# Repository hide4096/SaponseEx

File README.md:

# SaponseEx
マイクロマウス
RT社HM-Starterキットをベースに開発

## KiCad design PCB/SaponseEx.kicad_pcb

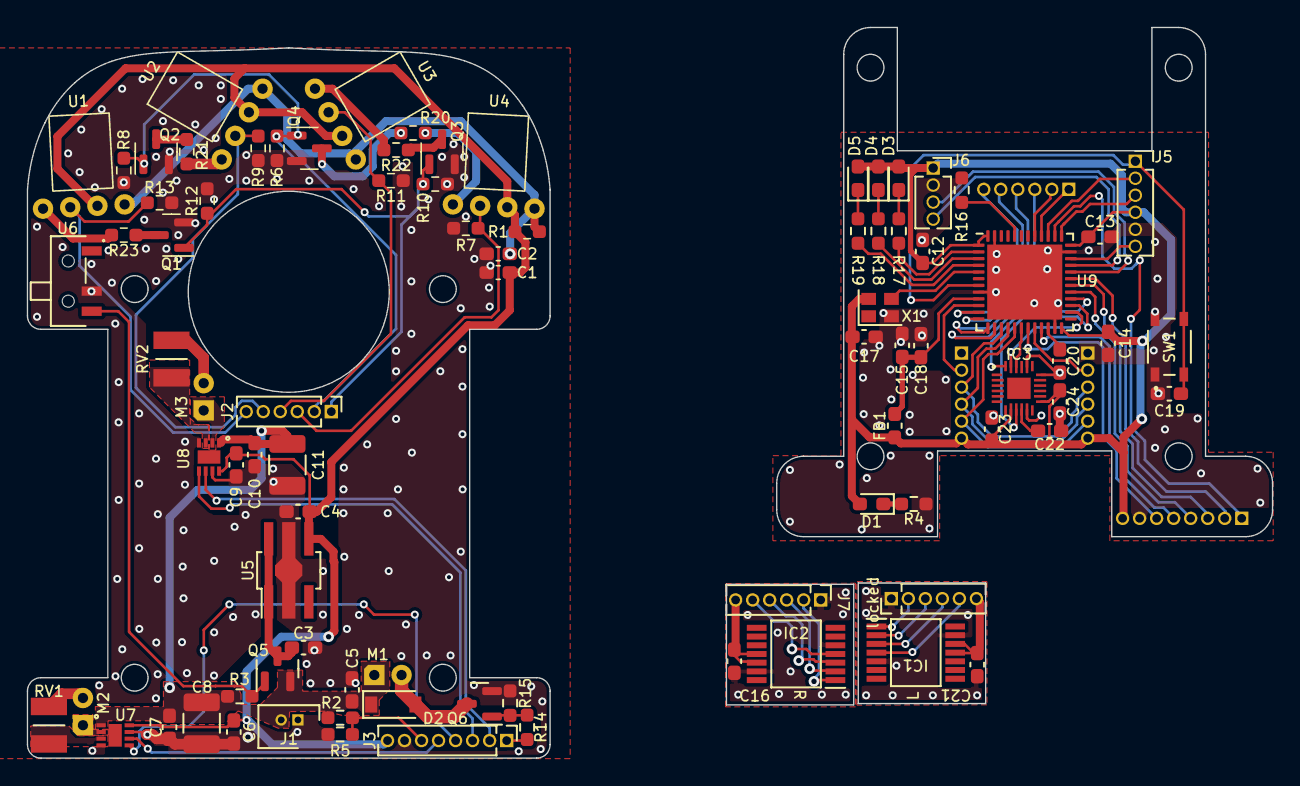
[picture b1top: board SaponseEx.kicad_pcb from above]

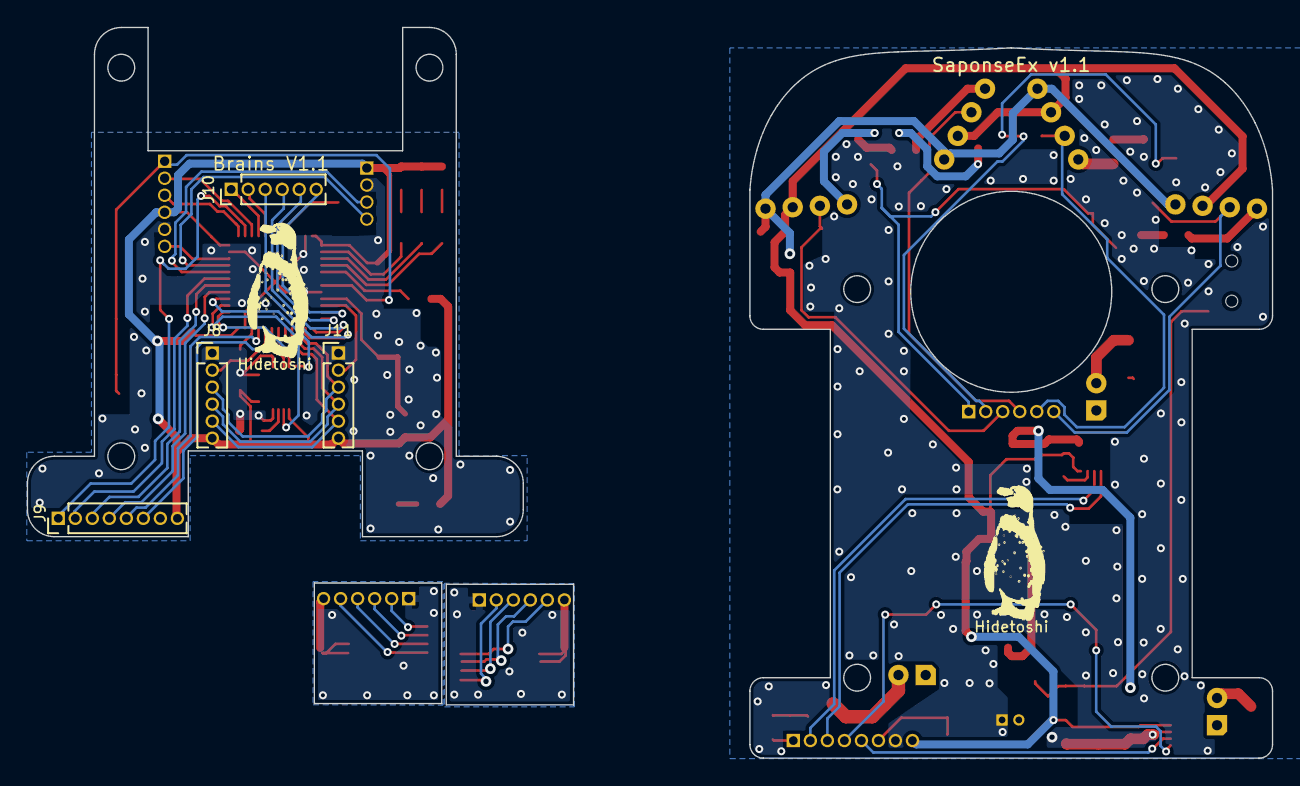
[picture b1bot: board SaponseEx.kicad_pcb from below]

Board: 2 copper layers, 92.9 x 54.5 mm, 89 parts (4 on the bottom side), 61 nets.

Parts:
C1, C2, C15: 1μ; C_0603_1608Metric_Pad1.08x0.95mm_HandSolder
C3: 0.33μ; C_0603_1608Metric_Pad1.08x0.95mm_HandSolder
C4: 2.2μ; C_0603_1608Metric_Pad1.08x0.95mm_HandSolder
C5, C6, C7, C9, C10, C12, C13, C14, C16, C17, C18, C19, C21, C22, C23, C24: 0.1μ; C_0603_1608Metric_Pad1.08x0.95mm_HandSolder
C8, C11: 47μ; C_1210_3225Metric_Pad1.33x2.70mm_HandSolder
C20: 4.7μ; C_0603_1608Metric_Pad1.08x0.95mm_HandSolder
D1, D3, D4, D5: LED; LED_0603_1608Metric_Pad1.05x0.95mm_HandSolder
D2: 1N4148W; D_SOD-123
FB1: FerriteBead; L_0603_1608Metric_Pad1.05x0.95mm_HandSolder
IC1, IC2: AS5047P-ATSM; SOP65P640X120-14N
IC3: ICM-20648; QFN40P300X300X95-25N-D
J1: CONN_BATT; SHDR2W35P0X125_1X2_425X320X420P
J2: Conn_A_Main; PinHeader_1x06_P1.27mm_Vertical
J3: Conn_B_Main; PinHeader_1x08_P1.27mm_Vertical
J5: SWD; PinSocket_1x06_P1.27mm_Vertical
J6: UART; PinSocket_1x04_P1.27mm_Vertical
J7: Conn_ENC_R; PinHeader_1x06_P1.27mm_Vertical
J8: Conn_MCU_R; PinHeader_1x06_P1.27mm_Vertical
J9: Conn_B_Sub; PinHeader_1x08_P1.27mm_Vertical
J10: Conn_A_Sub; PinHeader_1x06_P1.27mm_Vertical
J11: Conn_MCU_L; PinHeader_1x06_P1.27mm_Vertical
M1: Fan; Motor
M2, M3: MK06-4.5; Motor
Q1, Q2, Q3, Q4: BSS138; SOT-23
Q5: IRLML6402; SOT-23
Q6: IRLML6344; SOT-23
R1: 10; R_0603_1608Metric_Pad0.98x0.95mm_HandSolder
R2, R5, R16: 10k; R_0603_1608Metric_Pad0.98x0.95mm_HandSolder
R3, R6, R8, R10, R12, R15: 47k; R_0603_1608Metric_Pad0.98x0.95mm_HandSolder
R4, R17, R18, R19: 1k; R_0603_1608Metric_Pad0.98x0.95mm_HandSolder
R7, R9, R11, R13: 1M; R_0603_1608Metric_Pad0.98x0.95mm_HandSolder
R14: 30; R_0603_1608Metric_Pad0.98x0.95mm_HandSolder
R20, R21, R22, R23: 0; R_0603_1608Metric_Pad0.98x0.95mm_HandSolder
RV1, RV2: LBC3225T470KR; VARC3225X270N
SW1: RESET_SW; SKRPABE010
U1, U2, U3, U4: LBR-127HLD
U5: NJM2884; SOT-89-5_Handsoldering
U6: SSSS810701
U7, U8: DRV8212DSGR; SON50P200X200X80-9N
U9: STM32F412CGUx; QFN-48-1EP_7x7mm_P0.5mm_EP5.6x5.6mm
X1: SG-210STF; Oscillator_SMD_SeikoEpson_SG210-4Pin_2.5x2.0mm
locked: Conn_ENC_L; PinHeader_1x06_P1.27mm_Vertical

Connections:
+3V3: C1.1, C4.1, C6.1, C9.1, C12.2, C13.2, C14.2, C16.1, C17.1, C21.1, C23.1, C24.1, D1.2 (A), D3.2 (A), D4.2 (A), D5.2 (A), FB1.2, IC1.11 (VDD), IC1.12 (VDD3V), IC2.11 (VDD), IC2.12 (VDD3V), IC3.8 (VDDIO), IC3.13 (VDD), J3.8, J5.4, J6.1, J7.6, J8.6, J9.8, J11.6, R1.1, U1.3, U2.3, U3.3, U4.3, U5.4 (VOUT), U7.8 (VCC), U8.8 (VCC), U9.1 (VBAT), U9.24 (VDD), U9.36 (VDD), U9.48 (VDD), X1.4 (Vcc), locked.6
+BATT: C5.1, C7.1, C8.1, C10.1, C11.1, D2.1 (K), J1.2, M1.1 (+), Q5.2 (S), R2.1, R3.1, U7.1 (VM), U8.1 (VM)
CLK_ENC: IC1.2 (CLK), IC2.2 (CLK), J7.3, J8.3, J11.3, U9.15 (PA5), locked.3
CLK_IMU: IC3.23 (SCL_/_SCLK), U9.26 (PB13)
CS_IMU: IC3.22 (NCS), U9.18 (PB0)
CS_L: IC1.1 (CSN), J11.2, U9.10 (PA0), locked.2
CS_R: IC2.1 (CSN), J7.2, J8.2, U9.20 (PB2)
FAN_PWM: J3.1, J9.1, R14.1, U9.38 (PA15)
GND: C1.2, C2.2, C3.2, C4.2, C5.2, C6.2, C7.2, C8.2, C9.2, C10.2, C11.2, C12.1, C13.1, C14.1, C15.2, C16.2, C17.2, C18.2, C19.2, C20.1, C21.2, C22.2, C23.2, C24.2, IC1.5 (TEST), IC1.13 (GND), IC2.5 (TEST), IC2.13 (GND), IC3.11 (FSYNC), IC3.18 (GND), IC3.20 (RESV), J1.1, J3.7, J5.5, J6.2, J7.1, J8.1, J9.7, J11.1, Q1.2 (S), Q2.2 (S), Q3.2 (S), Q4.2 (S), Q6.2, R4.2, R5.2, R6.2, R7.2, R8.2, R9.2, R10.2, R11.2, R12.2, R13.2, R15.2, R16.1, SW1.1 (A), SW1.2 (A), U5.2 (GND), U6.2, U7.4 (GND), U7.7 (MODE), U8.4 (GND), U8.7 (MODE), U9.8 (VSSA), U9.23 (VSS), U9.35 (VSS), U9.47 (VSS), U9.49 (VSS), X1.2 (GND), locked.1
LED_FL_R: J2.2, J10.2, Q2.1 (G), Q4.1 (G), R6.1, R8.1, U9.41 (PB5)
LED_FR_L: J2.1, J10.1, Q1.1 (G), Q3.1 (G), R10.1, R12.1, U9.40 (PB4)
MISO_ENC: IC1.3 (MISO), IC2.3 (MISO), J7.4, J8.4, J11.4, U9.16 (PA6), locked.4
MISO_IMU: IC3.9 (SDO_/_AD0), U9.27 (PB14)
MOSI_ENC: IC1.4 (MOSI), IC2.4 (MOSI), J7.5, J8.5, J11.5, U9.17 (PA7), locked.5
MOSI_IMU: IC3.24 (SDA_/_SDI), U9.28 (PB15)
MOT_L_IN1: J3.2, J9.2, U8.6 (IN1), U9.31 (PA10)
MOT_L_IN2: J3.3, J9.3, U8.5 (IN2), U9.30 (PA9)
MOT_R_IN1: J3.5, J9.5, U7.6 (IN1), U9.21 (PB10)
MOT_R_IN2: J3.4, J9.4, U7.5 (IN2), U9.29 (PA8)
NRST: C19.1, J5.1, SW1.3 (B), SW1.4 (B), U9.7 (NRST)
unnamed: C2.1, R1.2, U1.1, U2.1, U3.1, U4.1
unnamed: C3.1, Q5.3 (D), U5.1 (CONTROL), U5.5 (VIN)
unnamed: C15.1, C18.1, FB1.1, U9.9 (VDDA)
unnamed: C20.2, U9.22 (VCAP_1)
unnamed: C22.1, IC3.10 (REGOUT)
unnamed: D1.1 (K), R4.1
unnamed: D2.2 (A), M1.2 (-), Q6.3
unnamed: D3.1 (K), R17.1
unnamed: D4.1 (K), R18.1
unnamed: D5.1 (K), R19.1
unnamed: M2.1 (+), U7.2 (OUT1)
unnamed: M2.2 (-), RV1.1
unnamed: M3.1 (+), U8.2 (OUT1)
unnamed: M3.2 (-), RV2.1
unnamed: Q1.3 (D), R23.1
unnamed: Q2.3 (D), R21.1
unnamed: Q3.3 (D), R22.1
unnamed: Q4.3 (D), R20.1
unnamed: Q5.1 (G), R3.2, U6.3
unnamed: Q6.1, R14.2, R15.1
unnamed: R16.2, U9.44 (BOOT0)
unnamed: R17.2, U9.2 (PC13)
unnamed: R18.2, U9.3 (PC14)
unnamed: R19.2, U9.4 (PC15)
unnamed: R20.2, U4.2
unnamed: R21.2, U2.2
unnamed: R22.2, U3.2
unnamed: R23.2, U1.2
unnamed: RV1.2, U7.3 (OUT2)
unnamed: RV2.2, U8.3 (OUT2)
unnamed: U9.5 (PH0), X1.3 (OUT)
SENS_FL: J2.5, J10.5, R9.1, U2.4, U9.12 (PA2)
SENS_FR: J2.4, J10.4, R11.1, U3.4, U9.13 (PA3)
SENS_L: J2.6, J10.6, R13.1, U1.4, U9.11 (PA1)
SENS_R: J2.3, J10.3, R7.1, U4.4, U9.14 (PA4)
SWCLK: J5.3, U9.37 (PA14)
SWDIO: J5.6, U9.34 (PA13)
SWO: J5.2, U9.39 (PB3)
UART_RX: J6.4, U9.33 (PA12)
UART_TX: J6.3, U9.32 (PA11)
VBATT: J3.6, J9.6, R2.2, R5.1, U9.19 (PB1)

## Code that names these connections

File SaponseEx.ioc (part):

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Mcu.Name=STM32F412C(E-G)Ux
Mcu.Package=UFQFPN48
Mcu.UserName=STM32F412CGUx
PA0.GPIOParameters=GPIO_Label
PA0.GPIO_Label=CS_L
PA0.Signal=GPIO_Output
PA1.GPIOParameters=GPIO_Label
PA1.GPIO_Label=SENS_L
PA1.Signal=ADCx_IN1
PA10.GPIOParameters=GPIO_Label
PA10.GPIO_Label=MOT_L_IN1
PA10.Signal=S_TIM1_CH3
PA11.Mode=Asynchronous
PA11.Signal=USART6_TX
PA12.Mode=Asynchronous
PA12.Signal=USART6_RX
PA13.Mode=Trace_Asynchronous_SW
PA13.Signal=SYS_JTMS-SWDIO
PA14.Mode=Trace_Asynchronous_SW
PA14.Signal=SYS_JTCK-SWCLK
PA15.GPIOParameters=GPIO_Label
PA15.GPIO_Label=FAN
PA15.Signal=GPIO_Output
PA2.GPIOParameters=GPIO_Label
PA2.GPIO_Label=SENS_FL
PA2.Signal=ADCx_IN2
PA3.GPIOParameters=GPIO_Label
PA3.GPIO_Label=SENS_FR
PA3.Signal=ADCx_IN3
PA4.GPIOParameters=GPIO_Label
PA4.GPIO_Label=SENS_R
PA4.Signal=ADCx_IN4
PA5.GPIOParameters=GPIO_Label
PA5.GPIO_Label=CLK_ENC
PA5.Mode=Full_Duplex_Master
PA5.Signal=SPI1_SCK
PA6.GPIOParameters=GPIO_Label
PA6.GPIO_Label=MISO_ENC
PA6.Mode=Full_Duplex_Master
PA6.Signal=SPI1_MISO
PA7.GPIOParameters=GPIO_Label
PA7.GPIO_Label=MOSI_ENC
PA7.Mode=Full_Duplex_Master
PA7.Signal=SPI1_MOSI
PA8.GPIOParameters=GPIO_Label
PA8.GPIO_Label=MOT_R_IN2
PA8.Signal=S_TIM1_CH1
PA9.GPIOParameters=GPIO_Label
PA9.GPIO_Label=MOT_L_IN2
PA9.Signal=S_TIM1_CH2
PB0.GPIOParameters=GPIO_Label
PB0.GPIO_Label=CS_IMU
PB0.Signal=GPIO_Output
PB1.GPIOParameters=GPIO_Label
PB1.GPIO_Label=VBATT
PB1.Signal=ADCx_IN9
PB10.GPIOParameters=GPIO_Label
PB10.GPIO_Label=MOT_R_IN1
PB10.Signal=S_TIM2_CH3
PB13.GPIOParameters=GPIO_Label
PB13.GPIO_Label=CLK_IMU
PB13.Mode=Full_Duplex_Master
PB13.Signal=SPI2_SCK
PB14.GPIOParameters=GPIO_Label
PB14.GPIO_Label=MISO_IMU
PB14.Mode=Full_Duplex_Master
PB14.Signal=SPI2_MISO
PB15.GPIOParameters=GPIO_Label
PB15.GPIO_Label=MOSI_IMU
PB15.Mode=Full_Duplex_Master
PB15.Signal=SPI2_MOSI
PB2.GPIOParameters=GPIO_Label
PB2.GPIO_Label=CS_R
PB2.Signal=GPIO_Output
PB3.Mode=Trace_Asynchronous_SW
PB3.Signal=SYS_JTDO-SWO
PB4.GPIOParameters=GPIO_Label
PB4.GPIO_Label=LED_FR_L
PB4.Signal=GPIO_Output
PB5.GPIOParameters=GPIO_Label
PB5.GPIO_Label=LED_FL_R
PB5.Signal=GPIO_Output
PC13.GPIOParameters=GPIO_Label
PC13.GPIO_Label=D3
PC13.Signal=GPIO_Output
PC14-OSC32_IN.GPIOParameters=PinState,GPIO_Label
PC14-OSC32_IN.GPIO_Label=D4
PC14-OSC32_IN.PinState=GPIO_PIN_RESET
PC14-OSC32_IN.Signal=GPIO_Output
PC15-OSC32_OUT.GPIOParameters=GPIO_Label
PC15-OSC32_OUT.GPIO_Label=D5
PC15-OSC32_OUT.Signal=GPIO_Output
PH0\ -\ OSC_IN.Mode=HSE-External-Clock-Source
PH0\ -\ OSC_IN.Signal=RCC_OSC_IN
PH1\ -\ OSC_OUT.Mode=HSE-External-Clock-Source
PH1\ -\ OSC_OUT.Signal=RCC_OSC_OUT
RCC.HSE_VALUE=20000000
RCC.SYSCLKFreq_VALUE=100000000
RCC.SYSCLKSource=RCC_SYSCLKSOURCE_PLLCLK
board=custom

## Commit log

2022-07-28 add readme
2022-07-30 赤外線センサにFFTでフィルタを追加
2022-07-30 [update]センサのフーリエ変換を手実装
2022-07-30 [update]DSPLIbraryを削除
2022-07-30 [fix]フーリエ変換の処理を見直し(実機まだ)
2022-07-30 [fix]バグを修正（実機まだ）
2022-07-31 [fix]フィルタ使わない方がいいじゃん
2022-08-01 [update]センサー、モータ制御追加
2022-08-02 [update]モータ制御、Panic追加
2022-08-02 [fix]センサの初期化処理を修正
2022-08-03 [fix]PWMのstart忘れを修正
2022-08-03 [update]速度計算追加
2022-08-03 [update]速度、角速度取得
2022-08-03 [update]ドリフト修正
2022-08-03 [update]速度、角度制御を簡易的に実装(Pだけだけど)
2022-08-03 [update]メニュー実装
2022-08-05 [fix]バッテリ残量を補正
2022-08-07 [fix]ローパスフィルタのゲインを調整
2022-10-14 [add]CADデータを追加
2022-10-14 [update]モーターマウントを改良
2022-10-14 [update]スカート追加
2022-10-14 [update]ファンいじった
2022-10-19 [update]IMUドライバ変更
2022-10-19 [update]IMUドライバを変更
2022-10-19 [fix]一部処理を分割
2022-10-19 [fix]エンコーダードライバを移動
2022-10-19 [fix]gitignoreを反映
2022-10-19 [fix]gitignore反映
2022-10-19 [add]ファイル分割した
2022-10-19 [fix]IMUの感度変更を改良
2022-10-19 [update]PID追加
2022-10-19 [fix]メニュー修正
2022-10-19 [fix]初期化を修正
2022-10-21 [update]宴会芸を追加
2022-10-23 [update]壁センサを省電力化
2022-10-23 [fix]モータカット機能を修正
2022-10-23 [update]あ
2022-10-28 [update]タイマー割り込みの周波数を5kHzにした
2022-10-28 [fix]ファンのトリガー処理を変更
2022-10-28 [fix]速度や角速度の単位を修正
2022-10-28 [fix]変数名ちゃんと変えてなかった
2022-10-28 [update]自動生成のコードを分離
2022-10-28 [add]buildディレクトリ追加
2022-10-28 [fix]速度計算を修正
2022-10-28 [fix]buildディレクトリやっぱ消す
2022-10-28 [update]ゲイン調整
2022-10-28 [update]壁制御追加
2022-10-28 [fix]壁制御のゲイン調整
2022-10-29 [fix]壁センサのDMA処理がまずかった
2022-10-29 [update]壁補正追加
2022-11-04 [fix]げいんちょうせい
2022-11-17 [fix]IMUの初期化処理を修正
2022-11-20 [update]タイマーの設定とSPIの速度を変更
2022-11-20 [fix]曲芸のやつを修正
2022-11-20 [fix]モード選択の処理を修正
2022-11-20 [fix]さっきのビルド通らなかったので修正
2022-11-20 [add]タイマー追加
2022-11-20 [update]モータ制御の処理を変更
2022-11-20 [add]壁制御を追加
2022-11-20 [add]とりあえず直進の処理書いた
2022-11-20 [fix]走るようにした
2022-11-20 [fix]壁センサの不具合を修正
2022-11-21 [fix]直進の巡行までの処理を修正
2022-11-21 [fix]無限走行に陥るバグを修正
2022-11-21 [add]旋回を実装した
2022-11-22 [fix]ちゃんとターンした
2022-11-22 [fix]しっかり旋回したよ
2022-11-22 [fix]ヘッダファイルの関係を修正
2022-11-22 [fix]グローバル変数の定義が冗長だったので整理
2022-11-22 [add]探索走行作るよ
2022-11-22 [add]足立法の機能ちょっと書いた
2022-11-22 [update]足立法もうちょい書いた
2022-11-22 [update]足立法を実装
2022-11-23 [fix]迷路は解けてそう
2022-11-25 [fix]ゲイン調整
2022-11-26 [fix]IMUの生値からの変換処理を修正
2022-11-26 [fix]Straightを修正
2022-11-26 [fix]走行の処理を修正
2022-11-26 [fix]CWCCWが逆でした
2022-11-26 [update]SPI読み取り速度アップ
2022-11-26 [fix]デバッグ用処理抜いた
2022-11-26 [fix]回転方向が逆でした
2022-11-26 [update]ヘッダファイルの関数の定義を改良
2022-11-26 [fix]旋回処理を修正
2022-11-26 [fix]電圧を校正
2022-11-26 [update]ゴール座標変更
2022-11-26 [update]ADCの読み方を改良
2022-11-26 [update]壁センサの発光パターン変えた
2022-12-09 [add]BLE機能を追加
2022-12-09 [fix]iocファイル反映
2022-12-10 [fix]ITM_SendCharを修正
2022-12-10 [fix]グラフ描画を追加
2022-12-10 [add]グラフ追加
2022-12-18 [update]PWMの与え方を変更
2022-12-18 [add]モーターテスト処理を追加
2022-12-18 [add]PWMモードを切り替えられるようにした
2022-12-18 [add]PWM方式切り替え機能の追加
2022-12-18 [update]キャリア周波数をいい感じに変化させる
2022-12-20 [fix]壁センサの配線ミスを修正
2022-12-20 [update]ADC回り足してみた
2022-12-22 [update]ADC調整
2022-12-22 [update]任意電圧を印加できるようにした
2022-12-22 [add]メモリ消去を追加
2022-12-22 [update]ログ機能追加(いろいろ壊すけど)
2022-12-22 [fix].gitignoreを修正
2022-12-22 [fix]領域外に書き込んじゃってた
2022-12-22 [update]システム同定を適用
2022-12-25 [add]システム同定やってみた
2022-12-25 [fix]PID処理全然違うじゃん
2022-12-26 [update]ログ形式変えた
2022-12-26 [update]制御をちょっと変えた
2023-01-11 [fix]モタドラのスリープ回避
2023-01-11 [fix]PWMの設定がミスってた
2023-01-13 [update]相補フィルタを追加
2023-01-15 [fix]spinturnの減速処理修正
2023-01-15 [update]ゲイン調整完了
2023-01-15 [add]壁センサをグラフに出力
2023-01-15 [update]iocファイルとの整合性とった
2023-01-16 [add]OC追加
2023-01-16 [add]壁センサ読み取り書き換え
2023-01-16 [fix]とりあえず読んだ
2023-01-17 [fix]タイヤのゴム脱落を防止
2023-01-28 [fix]ギアホイール改修
2023-01-28 [add]ログ吐き追加
2023-01-28 [add]ADCのウェイトをまとめた
2023-01-28 [update]読み方変えたけど...
2023-01-28 [fix]先輩は絶対値取ってた
2023-01-28 [fix]タイマー調整
2023-01-28 [fix]発光パターンを修正
2023-01-28 [add]マップ吐き出し
2023-01-29 [fix]マップ修正
2023-01-30 [fix]壁を検知できなかったときに範囲外にアクセスするバグを修正
2023-02-05 [add]壁センサのログとる
2023-02-05 [add]角度調整する
2023-02-05 [fix]直線走行のバグを修正
2023-02-05 [fix]前壁の判定を変更
2023-02-05 [fix]壁設置のバグ修正
2023-02-05 [fix]足立法のバグ修正
2023-02-08 [update]ADC読み取りをポーリングに変更
2023-02-08 [update]リポ電圧の監視を修正
2023-02-08 [fix]壁制御のゲインを調整
2023-02-14 [fix]壁補正の符号が反転してた
2023-02-14 [add]壁センサログ追加
2023-02-14 [fix]センサ値表示を綺麗にした
2023-02-14 [add]オドメトリ追加
2023-02-14 [add]座標をログに書き込み
2023-02-14 [add]ログ周期変更
2023-02-14 [add]吸引ファン作った
2023-02-15 [add]吸引ファン修正
2023-02-15 [add]軌道追従を実装した,,,?
2023-02-18 [add]スラローム追加
2023-02-18 [fix]Dゲインの処理がおかしかった
2023-02-18 [fix]壁補正の閾値を修正
2023-02-18 [fix]スラローム調整
2023-03-04 [add]吸引ファン試験機追加
2023-03-04 [add]ファン追加
2023-04-05 [fix]gitignore編集
2023-04-05 [fix]コミットし直した
2023-04-05 [fix]コミットし直し
2023-06-16 [fix]配線変更
2023-06-24 [update]iocファイルをアップデート CubeMX6.8.0に対応
2023-06-24 [update]イチからやり直す
2023-06-24 [update]HelloWorld
2023-06-24 [add]エンコーダーのドライバ書き始めた
2023-06-27 [add]エンコーダーのドライバ動かん
2023-06-27 [add]エンコーダーの初期化処理書いたけど動かん
2023-06-27 [try]TransmitRecieveにしたけど変化なし
2023-06-28 [fix]AS5047p動かん
2023-06-28 [try]既存のドライバー試す
2023-06-28 [add]初期化処理追加
2023-06-28 [update]手動でも読めたっぽい
2023-06-28 [update]手動で読めるじゃん
2023-06-28 [fix]CS上げ下げしないと動かんのかいw
2023-06-29 [update]角度読み取り付けたけどエラー出る
2023-06-29 [add]読めるけどエラー吐く
2023-06-29 [fix]読めたわ
2023-06-29 [update]エンコーダードライバ動いた
2023-06-29 [add]エンコーダーに初期化判定追加
2023-06-30 [update]エンコーダードライバでけた
2023-06-30 [add]モタドラ制御追加
2023-06-30 [add]モタドラのドライバ書いた
2023-06-30 [fix]モタドラ書けた?
2023-06-30 [update]ピンの設定した
2023-06-30 [fix]型直した
2023-07-07 [fix]逆回転の出力がバグってた
2023-07-07 [update]モタドラを修正
2023-07-07 [add]割り込み追加
2023-07-07 [add]速度制御を追加
2023-07-08 [add]ADC追加しよ
2023-07-08 [add]壁センサ読めるようになった
2023-07-09 [add]FF追加
2023-07-25 [fix]IMUのモード変更をチェック
2023-07-25 [add]フラッシュ追加
2023-07-26 [add]ロギング追加
2023-07-26 [add]加減速追加
2023-07-26 [add]モード切替追加
2023-07-26 [update]前後方向のFBゲイン削除
2023-07-26 [update]FFを一個のゲインにした
2023-07-26 [update]FFのゲインを切り替え
2023-07-26 [add]PIDFFの検証
2023-07-27 [add]IMU内蔵のLPFを有効化
2023-07-27 [add]vscodeの設定ファイルを保持
2023-07-27 [add]探索を実装してみた
2023-07-28 [update]直進と超信地旋回を実装
2023-07-28 [update]探索動かん
2023-07-29 [update]壁制御入れた
